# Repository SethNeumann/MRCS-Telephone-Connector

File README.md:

## License: Creative Commons Attribution-NonCommercial-ShareAlike

This board provides connectors to extend the MRCS power and phone bus (used by the EBF31A Battery Feed and ATSN Dispatcher/Operator Boards) to as many as 12 stations. Pads are provided for two bucking converters to develop 12VDC for buzzers, LEDs and Relay Latches and 7.5V for a Morse Code Buzzer Controller Board (MCBC).

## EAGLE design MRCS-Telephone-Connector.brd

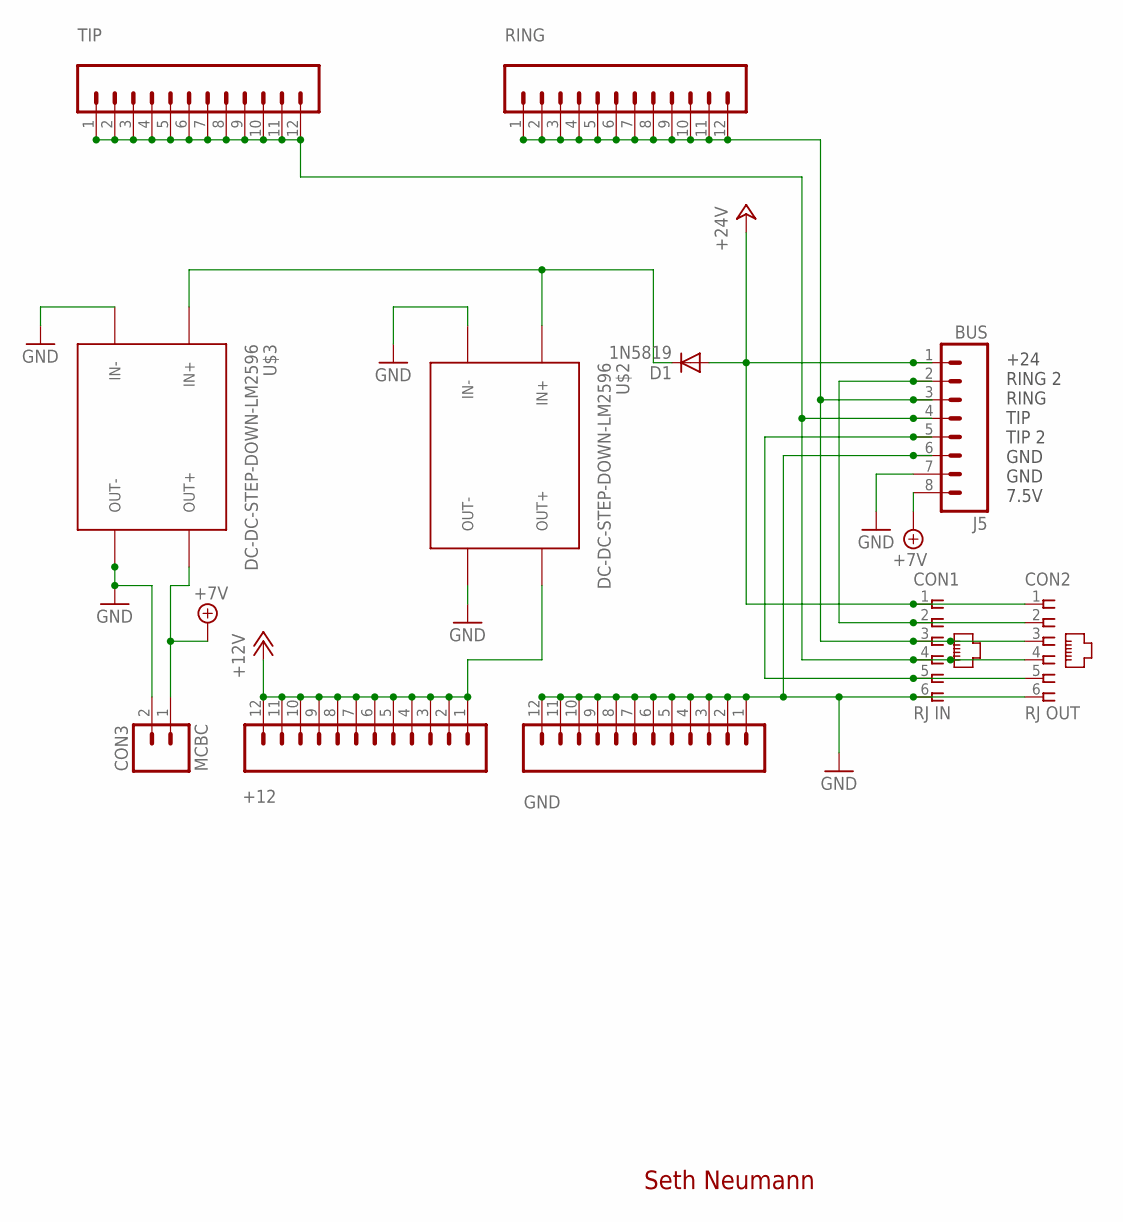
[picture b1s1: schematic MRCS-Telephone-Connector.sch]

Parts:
+12: CONNECTOR-M12LOCK; 1X12_LOCK
CON1: RJ IN; RJ25-INVERTED
CON2: RJ OUT; RJ25-INVERTED
CON3: MCBC; 1X02-2MM
D1: 1N5819; DIODE-1N4001
GND: CONNECTOR-M12LOCK; 1X12_LOCK
J5: BUS; 1X08_LOCK
RING: CONNECTOR-M12LOCK; 1X12_LOCK
TIP: CONNECTOR-M12LOCK; 1X12_LOCK
U$2, U$3: DC-DC-STEP-DOWN-LM2596

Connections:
+7V: CON3.1 (A), J5.8, U$3.OUT+
+12V: +12.1, +12.2, +12.3, +12.4, +12.5, +12.6, +12.7, +12.8, +12.9, +12.10, +12.11, +12.12, U$2.OUT+
+24V: CON1.1, CON2.1, D1.A, J5.1
GND: CON1.6, CON2.6, CON3.2 (B), GND.1, GND.2, GND.3, GND.4, GND.5, GND.6, GND.7, GND.8, GND.9, GND.10, GND.11, GND.12, J5.6, J5.7, U$2.IN-, U$2.OUT-, U$3.IN-, U$3.OUT-
unnamed: D1.C, U$2.IN+, U$3.IN+
RING: CON1.3, CON2.3, J5.3, RING.1, RING.2, RING.3, RING.4, RING.5, RING.6, RING.7, RING.8, RING.9, RING.10, RING.11, RING.12
RING2: CON1.2, CON2.2, J5.2
TIP: CON1.4, CON2.4, J5.4, TIP.1, TIP.2, TIP.3, TIP.4, TIP.5, TIP.6, TIP.7, TIP.8, TIP.9, TIP.10, TIP.11, TIP.12
TIP2: CON1.5, CON2.5, J5.5

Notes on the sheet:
Seth Neumann
+24 RING 2 RING TIP TIP 2 GND GND 7.5V

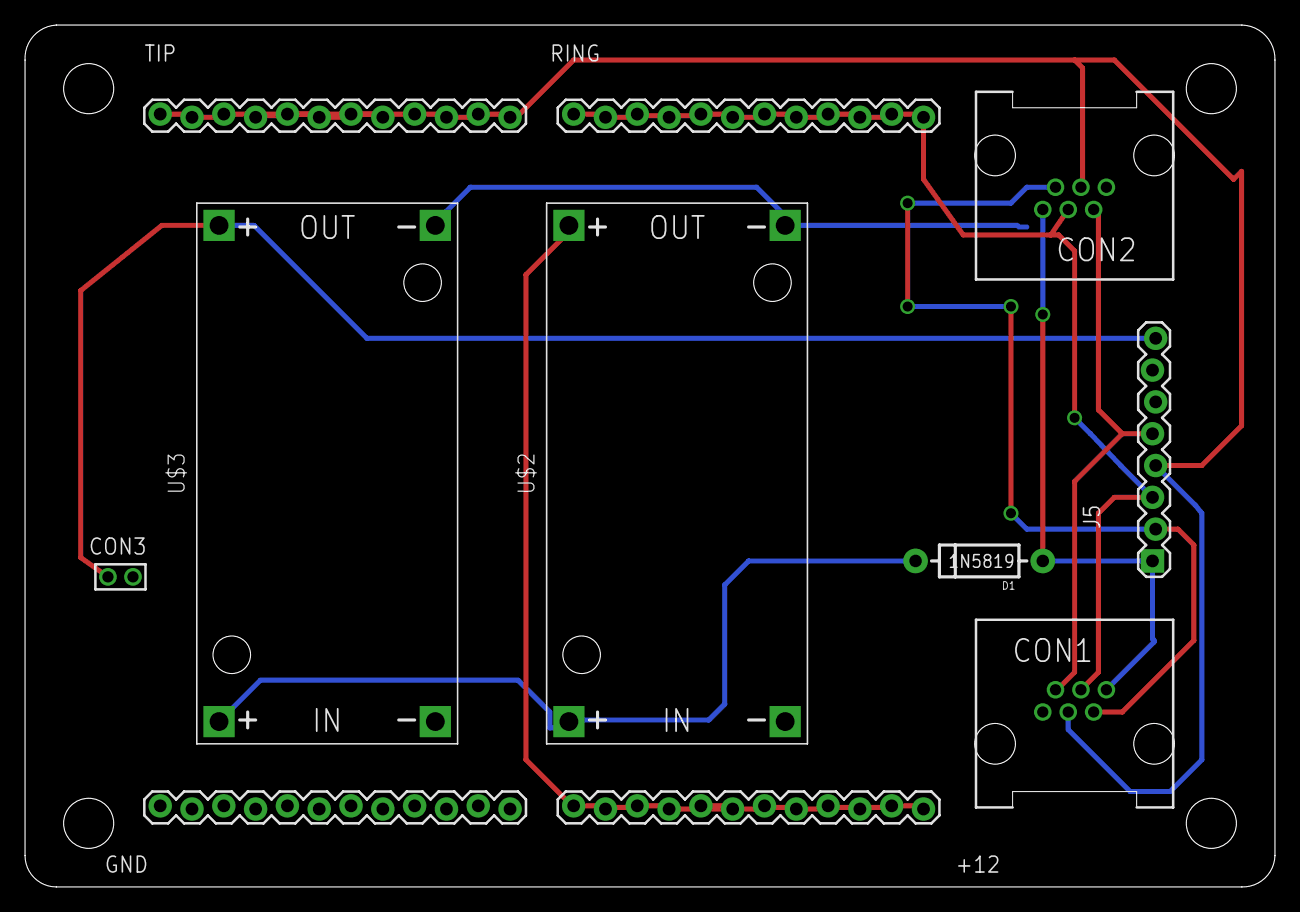
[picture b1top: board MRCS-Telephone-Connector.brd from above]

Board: 2 copper layers, 99.8 x 68.8 mm, 15 parts (0 on the bottom side), 9 nets.

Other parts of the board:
U$1: BOARD-DINRAIL-2.71IN-MRCS
U$4: MRCSLOGOTOP
U$5: MRCSLOGOBTM
U$6: CA-PROP65WARNING

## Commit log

2020-08-20 Update DESCRIPTION
2020-08-20 Update INFO
2020-08-20 intial commit
    initial commit
2020-08-20 added Bill of Materials
    Parts list
2020-08-23 Change Train Boss to TrainBoss
    Change Train Boss to TrainBoss, note about Schottky diode
2023-09-13 new eagle.epf file
    CHanged to version 2.1 added new schottkey diode

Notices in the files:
parts and their libraries:
diy-modules: Released under the Creative Commons Attribution 4.0 International License: http://creativecommons.org/licenses/by/4.0
